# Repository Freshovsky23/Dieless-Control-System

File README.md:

# Dieless - Automated Wire Drawing Control System 🧵⚙️⚡

An advanced embedded control system designed for a **Dieless Wire Drawing Machine** engineering project. This system coordinates independent dual-stepper motor velocity profiles, features real-time analog micro-adjustments, and utilizes a complete local Human-Machine Interface (HMI).

Developed under the auspices of the **"CREATIVE" Student Science Club**.

---

## 📺 Project Presentation & Demo

Watch the system in action on YouTube:

*Click the badge above to watch the project implementation and physical mechanical execution details.*

---

## 🚀 System Features

* **High-Performance Jitter-Free Engine:** Implements a non-blocking microsecond phase-accumulation scheduler capable of driving dual A4988 stepper drivers independently without timing drift.
* **Velocity Profiling (Ramp Rate):** Integrated linear acceleration and deceleration profiling (2000 Hz/s rate) protecting motors from stalling or losing synchronization during sudden load changes.
* **Real-Time Trim Adjustment:** Dual-potentiometer sampling with 12-bit ADC mapping, providing a precision $\pm5\%$ velocity override overlay on-the-fly.
* **4x4 Matrix Keypad Configuration:** Full operational control board layout using an asynchronous multi-state input buffer for entering specific base frequencies (Hz).
* **Optimized I2C HMI Display:** Formatted 20x4 LCD frame architecture running on a high-speed 400kHz I2C bus clock to eliminate screen update blocking latencies.

---

## 🛠️ Hardware & PCB Design

The control system has been migrated from breadboard prototyping to a dedicated, custom-designed PCB tailored for high-frequency signal switching and heavy motor current distribution. 

### 📐 PCB View (3D Render)
The board architecture implements strict physical isolation between the high-current motor power rails (VMOT) and the sensitive analog/I2C traces to completely eliminate electromagnetic interference and noise injection.

---

## 🔌 Complete Hardware Pin Mapping (Pinout)

To ensure proper hardware replication, connect the peripheral components to the ESP32 microcontroller precisely as outlined in the engineering reference tables below:

### 1. Actuators & Control Interfaces
| ESP32 GPIO Pin | Component Peripheral | Hardware Functionality / Description | Suggested Track Width |
| :---: | :--- | :--- | :---: |
| **+5V / VIN** | Main Logic Rail | Core power for driver logic and LCD module | **0.50 mm** |
| **+3.3V** | Analog Rail | Clean reference voltage for ADC potentiometers | **0.50 mm** |
| **VMOT (24V)** | A4988 Power Supply | High-current power for stepper motor coils | 🔥 **1.20 mm** |
| **GND** | System Common | Solid Ground Plane (Bottom Copper Zone) | *Copper Zone* |
| **GPIO 18** | Stepper Driver 1 (A4988) | **STEP** – Motor 1 Pulse Generation Line (Wire Feeding) | 0.25 mm |
| **GPIO 19** | Stepper Driver 1 (A4988) | **DIR** – Motor 1 Directional Logic Level Control | 0.25 mm |
| **GPIO 23** | Stepper Driver 2 (A4988) | **STEP** – Motor 2 Pulse Generation Line (Wire Drawing) | 0.25 mm |
| **GPIO 16** | Stepper Driver 2 (A4988) | **DIR** – Motor 2 Directional Control (*Safe Non-Bootstrap Pin*) | 0.25 mm |
| **GPIO 34** | Potentiometer 1 | **Analog Input** – Motor 1 Real-time Speed Trim Override | 0.25 mm |
| **GPIO 35** | Potentiometer 2 | **Analog Input** – Motor 2 Real-time Speed Trim Override | 0.25 mm |
| **GPIO 4** | SPDT Toggle Switch | **Digital Input (Internal Pullup)** – Active Motor Selection Editor | 0.25 mm |

### 2. 4x4 Membrane Keypad Matrix Connections
| ESP32 GPIO Pin | Keypad Ribbon Pin | Matrix Row / Column Designation | Suggested Track Width |
| :---: | :---: | :--- | :---: |
| **GPIO 13** | Pin 1 | **ROW 1** (Handles keys: 1, 2, 3, A) | 0.25 mm |
| **GPIO 14** | Pin 2 | **ROW 2** (Handles keys: 4, 5, 6, B) | 0.25 mm |
| **GPIO 27** | Pin 3 | **ROW 3** (Handles keys: 7, 8, 9, C) | 0.25 mm |
| **GPIO 26** | Pin 4 | **ROW 4** (Handles keys: \*, 0, #, D) | 0.25 mm |
| **GPIO 25** | Pin 5 | **COL 1** (Handles keys: 1, 4, 7, \*) | 0.25 mm |
| **GPIO 33** | Pin 6 | **COL 2** (Handles keys: 2, 5, 8, 0) | 0.25 mm |
| **GPIO 32** | Pin 7 | **COL 3** (Handles keys: 3, 6, 9, #) | 0.25 mm |
| **GPIO 17** | Pin 8 | **COL 4** (Handles keys: A, B, C, D) | 0.25 mm |

### 3. Display Peripherals & Bus Communication
| ESP32 GPIO Pin | Module / Controller | Bus Line Designation | Suggested Track Width |
| :---: | :--- | :--- | :---: |
| **GPIO 21** | I2C LCD 20x4 (PCF8574) | **SDA** – Serial Data Communication Bus | 0.25 mm |
| **GPIO 22** | I2C LCD 20x4 (PCF8574) | **SCL** – Serial Clock Bus (Configured to 400kHz Fast Mode) | 0.25 mm |

---

## ⌨️ Control Panel HMI Reference

### Keypad 4x4 Layout Matrix

| Key | Core Function | Operational Description |
| :---: | :--- | :--- |
| **`0` – `9`** | **Numeric Entry** | Inputs target step frequency values (Safe bounded range: `0` – `9999` Hz). |
| **`D`** | **Direction Stage** | Toggles the pending rotational direction profile buffer layout between `[CW]` and `[CCW]`. |
| **`#`** | **ENTER / Commit** | Flushes the staged parameters, saving target velocity and setting hardware direction pins. |
| **`*`** | **Backspace** | Removes the terminal character from the active screen buffer string. |
| **`C`** | **Clear Buffer** | Instantly wipes the temporary keyboard data input buffer. |
| **`A`** | **START Machine** | Global execution trigger. Smoothly ramps up both stepper lines to target run frequencies. |
| **`B`** | **STOP Machine** | E-Stop equivalent software override. Instantly cuts execution pulses and triggers safe deceleration. |

### LCD 20x4 Screen Topology Reference
The user interface handles full frame updates seamlessly asynchronously. The display grid mapping topology layout runs as follows:

```text
+------------------------------------+
|M1: [BaseHz] |T:[Trim%] |[ActiveDir]| -> Line 1: Wire Feeding Motor Telemetry
|M2: [BaseHz] |T:[Trim%] |[ActiveDir]| -> Line 2: Wire Drawing Motor Telemetry
|Input: [EditorBuffer]   [PendingDir]| -> Line 3: Live Input HMI Keypad Buffer
|[MachineStatus] | Ed: [TargetMotor] | -> Line 4: System Operational Status
+------------------------------------+
📂 Repository Structure
Plaintext
├── firmware/              # ESP32 Core Control Source Code (C++/Arduino)
│   ├── src/
│   │   └── main.cpp
│   └── platformio.ini
├── hardware/              # KiCad EDA Project Files & Manufacturing Exports
│   ├── dieless-control.kicad_pro
│   ├── dieless-control.kicad_sch
│   ├── dieless-control.kicad_pcb
│   └── Dieless.png        # 3D Render preview of the custom PCB layout
└── README.md              # Main project documentation
👤 Author
Developer: @Freshovsky23

Contact: Heilman.Wiktor23@gmail.com

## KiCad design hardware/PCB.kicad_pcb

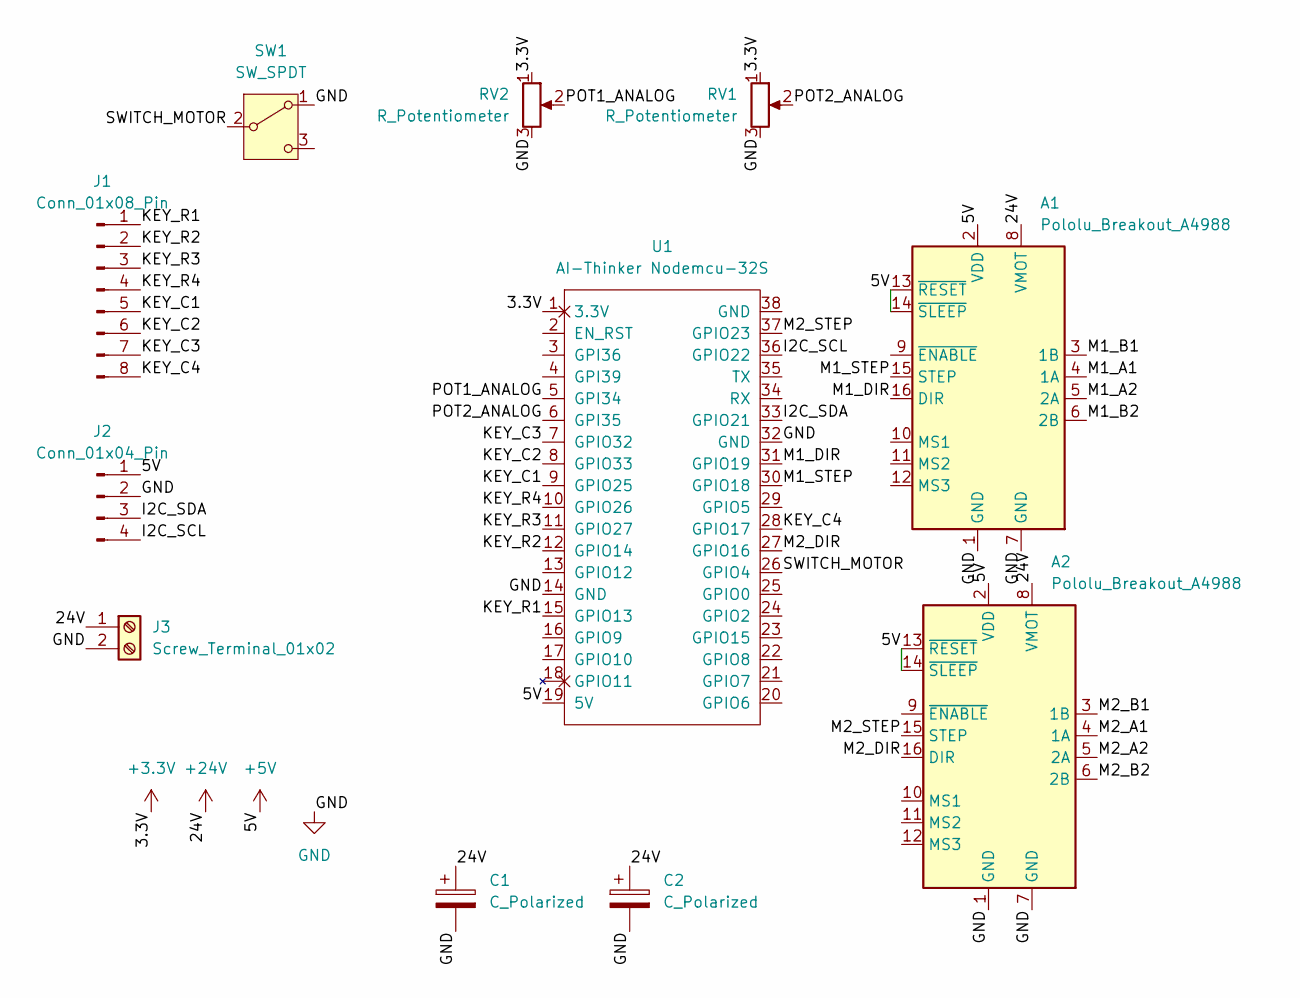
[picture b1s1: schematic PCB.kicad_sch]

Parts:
A1, A2: Pololu_Breakout_A4988; Pololu_Breakout-16_15.2x20.3mm
C1, C2: C_Polarized; CP_Radial_D8.0mm_P3.50mm
J1: Conn_01x08_Pin; PinHeader_1x08_P2.54mm_Vertical
J2: Conn_01x04_Pin; PinHeader_1x04_P2.54mm_Vertical
J3: Screw_Terminal_01x02; TerminalBlock_MaiXu_MX126-5.0-02P_1x02_P5.00mm
RV1, RV2: R_Potentiometer; Potentiometer_Bourns_3386P_Vertical
SW1: SW_SPDT; SW_Slide_SPDT_Straight_CK_OS102011MS2Q
U1: AI-Thinker Nodemcu-32S; ai-thinker nodemcu-32s

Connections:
+3.3V: RV1.1, RV2.1, U1.1 (3.3V)
+5V: A1.2 (VDD), A1.13 (~RESET), A1.14 (~SLEEP), A2.2 (VDD), A2.13 (~RESET), A2.14 (~SLEEP), J2.1, U1.19 (5V)
+24V: A1.8 (VMOT), A2.8 (VMOT), C1.1, C2.1, J3.1
/I2C_SCL: J2.4, U1.36 (GPIO22)
/I2C_SDA: J2.3, U1.33 (GPIO21)
/KEY_C1: J1.5, U1.9 (GPIO25)
/KEY_C2: J1.6, U1.8 (GPIO33)
/KEY_C3: J1.7, U1.7 (GPIO32)
/KEY_C4: J1.8, U1.28 (GPIO17)
/KEY_R1: J1.1, U1.15 (GPIO13)
/KEY_R2: J1.2, U1.12 (GPIO14)
/KEY_R3: J1.3, U1.11 (GPIO27)
/KEY_R4: J1.4, U1.10 (GPIO26)
/M1_A1: A1.4 (1A)
/M1_A2: A1.5 (2A)
/M1_B1: A1.3 (1B)
/M1_B2: A1.6 (2B)
/M1_DIR: A1.16 (DIR), U1.31 (GPIO19)
/M1_STEP: A1.15 (STEP), U1.30 (GPIO18)
/M2_A1: A2.4 (1A)
/M2_A2: A2.5 (2A)
/M2_B1: A2.3 (1B)
/M2_B2: A2.6 (2B)
/M2_DIR: A2.16 (DIR), U1.27 (GPIO16)
/M2_STEP: A2.15 (STEP), U1.37 (GPIO23)
/POT1_ANALOG: RV2.2, U1.5 (GPI34)
/POT2_ANALOG: RV1.2, U1.6 (GPI35)
/SWITCH_MOTOR: SW1.2 (B), U1.26 (GPIO4)
GND: A1.1 (GND), A1.7 (GND), A2.1 (GND), A2.7 (GND), C1.2, C2.2, J2.2, J3.2, RV1.3, RV2.3, SW1.1 (A), U1.14 (GND), U1.32 (GND)

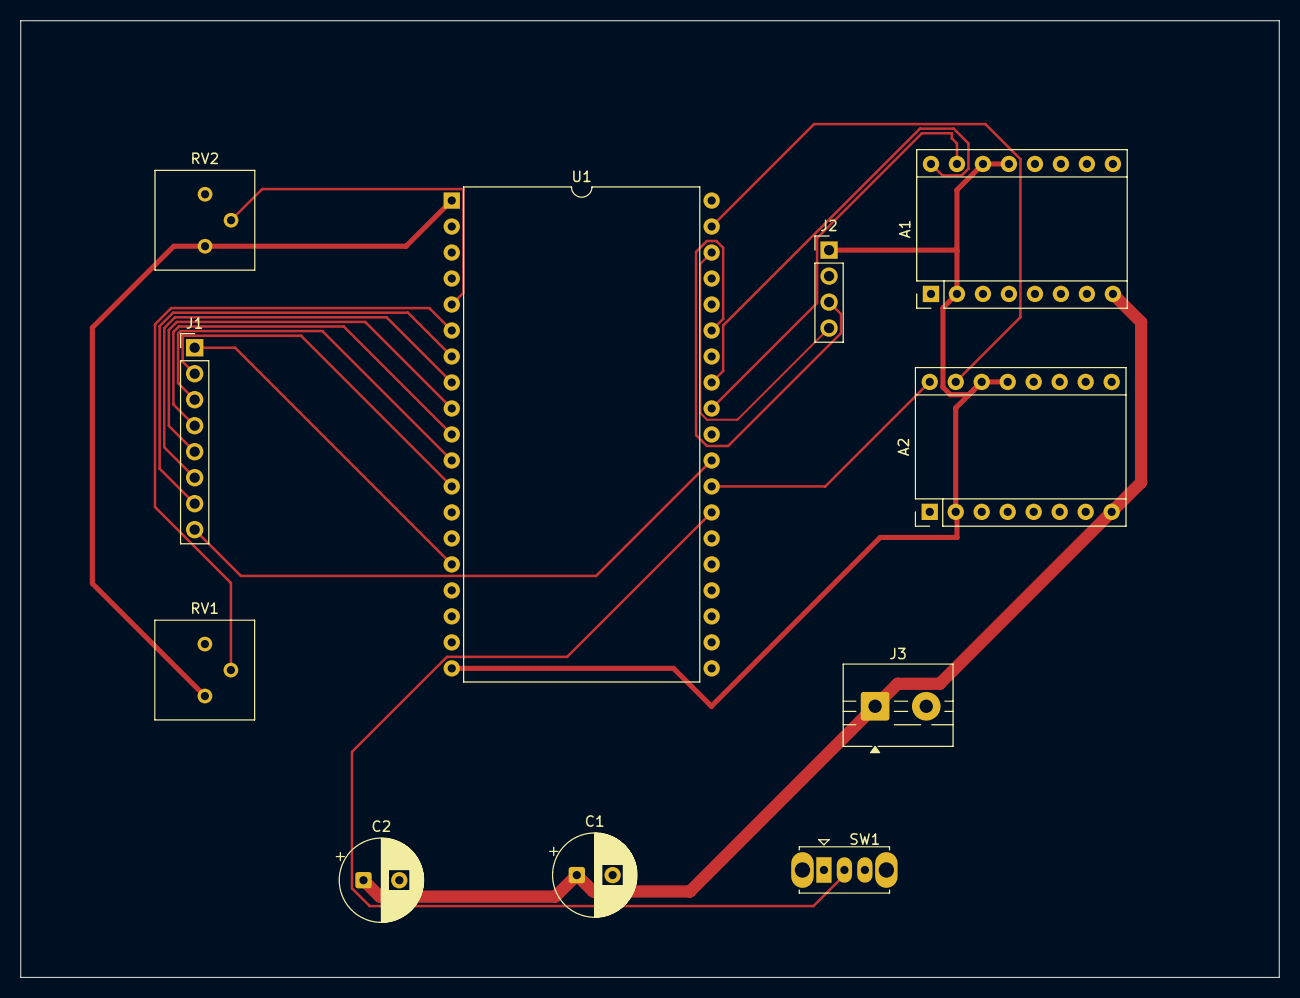
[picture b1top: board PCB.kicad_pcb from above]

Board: 2 copper layers, 123.0 x 93.5 mm, 11 parts (0 on the bottom side), 21 nets.

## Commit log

2026-06-04 Initial commit: Production ready Dieless automated control system
2026-06-06 Change YouTube demo link in README
    Updated YouTube link for project demo in README.
2026-06-07 feat: add initial KiCad schematic and PCB layout design
2026-06-07 Revise README with new features and PCB design details
    Updated README.md to enhance clarity and add new sections.
